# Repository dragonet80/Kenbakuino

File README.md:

# Kenbakuino
This is a fork from: https://github.com/funnypolynomial/Kenbakuino

This is in WIP state!

Arduino emulation of the KENBAK-1

This is an Arduino-based emulation of the 
[KENBAK-1](https://en.wikipedia.org/wiki/Kenbak-1 "Wikipedia"), considered by some to be the first "personal computer".  It was first advertised for sale in the September 1971 issue of Scientific American.

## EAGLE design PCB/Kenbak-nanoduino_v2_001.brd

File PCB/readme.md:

Fitxers per a la PCB en format Autodesk Eagle

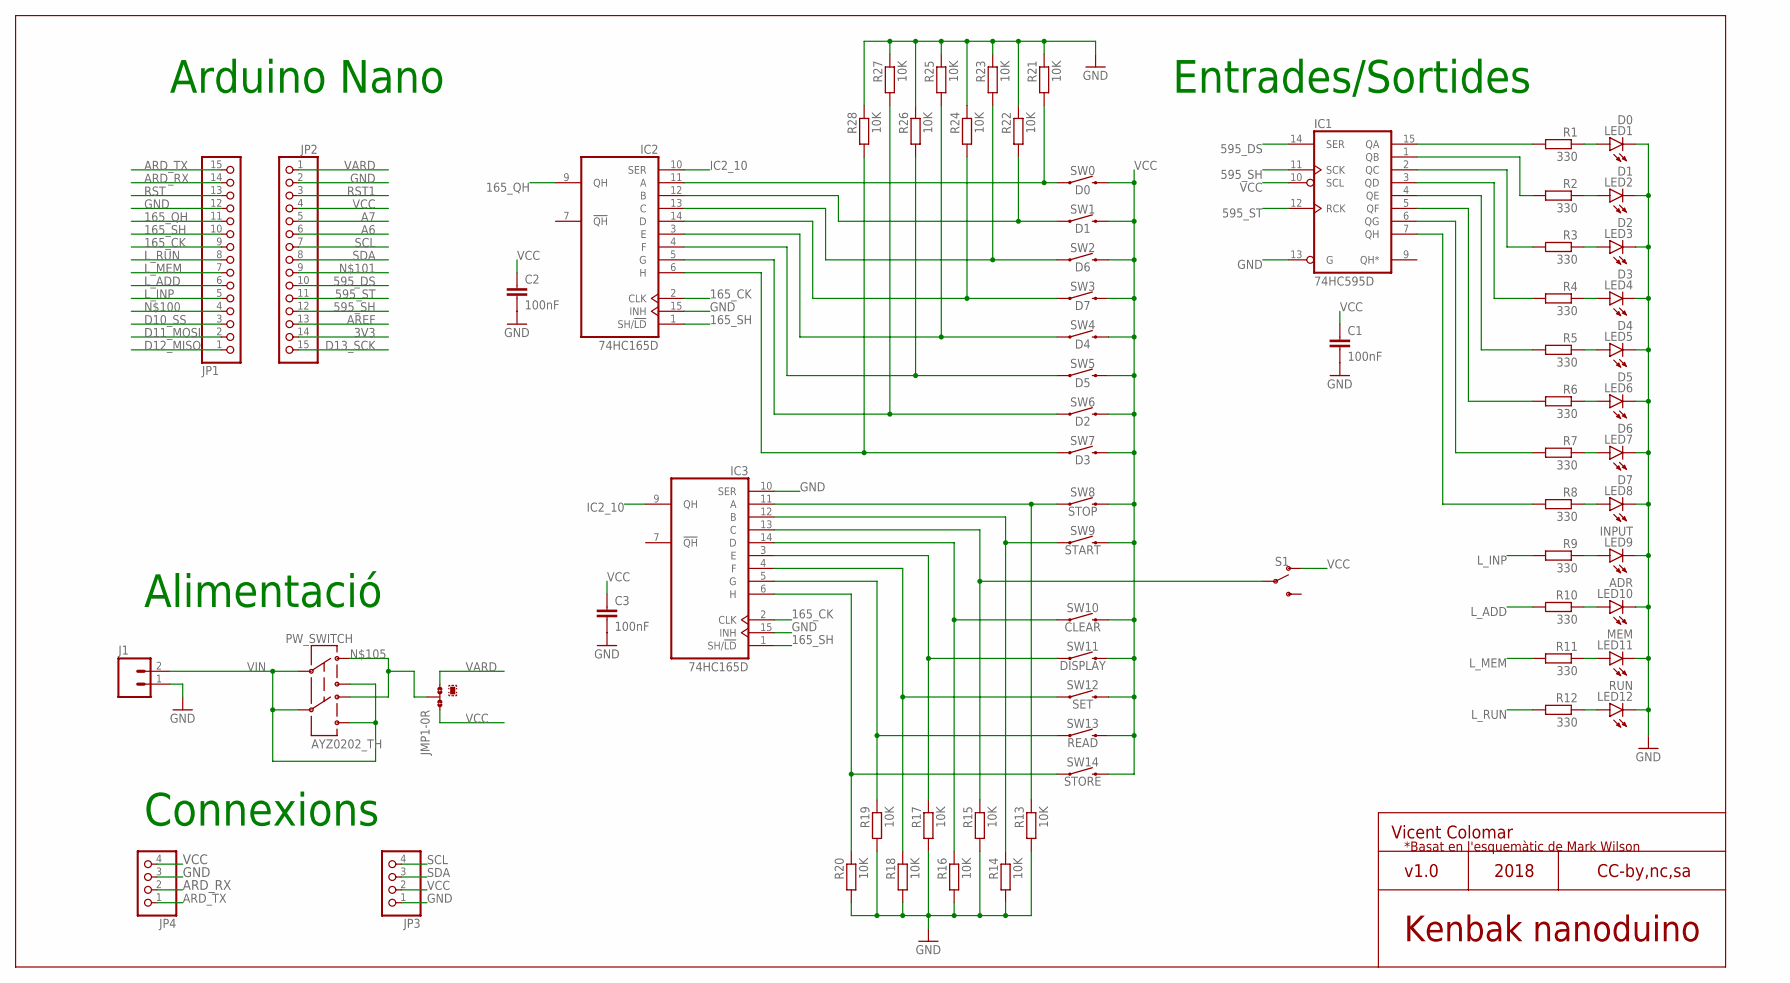
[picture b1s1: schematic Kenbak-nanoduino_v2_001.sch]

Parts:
C1, C2, C3: 100nF; C1206
IC1: 74HC595D; SO16
IC2, IC3: 74HC165D; SO16
J1: M02LOCK_LONGPADS; 1X02_LOCK_LONGPADS
JMP1: 0R-JUMPA; A0R-JMP
JP1, JP2: PINHD-1X15_2.54-SMD; 1X15SMD
JP3, JP4: PINHD-1X04_2.54-SMD; 1X04SMD
LED1: D0; LED3MM
LED2: D1; LED3MM
LED3: D2; LED3MM
LED4: D3; LED3MM
LED5: D4; LED3MM
LED6: D5; LED3MM
LED7: D6; LED3MM
LED8: D7; LED3MM
LED9: INPUT; LED3MM
LED10: ADR; LED3MM
LED11: MEM; LED3MM
LED12: RUN; LED3MM
PW_SWITCH: AYZ0202_TH
R1, R2, R3, R4, R5, R6, R7, R8, R9, R10, R11, R12: 330; R1206
R13, R14, R15, R16, R17, R18, R19, R20, R21, R22, R23, R24, R25, R26, R27, R28: 10K; R1206
S1: SWITCH-SPDT-PTH-11.6X4.0MM; SWITCH_SPDT_PTH_11.6X4.0MM
SW0: D0; TACTILE_SWITCH_SMD_6.0X3.5MM
SW1: D1; TACTILE_SWITCH_SMD_6.0X3.5MM
SW2: D6; TACTILE_SWITCH_SMD_6.0X3.5MM
SW3: D7; TACTILE_SWITCH_SMD_6.0X3.5MM
SW4: D4; TACTILE_SWITCH_SMD_6.0X3.5MM
SW5: D5; TACTILE_SWITCH_SMD_6.0X3.5MM
SW6: D2; TACTILE_SWITCH_SMD_6.0X3.5MM
SW7: D3; TACTILE_SWITCH_SMD_6.0X3.5MM
SW8: STOP; TACTILE_SWITCH_SMD_6.0X3.5MM
SW9: START; TACTILE_SWITCH_SMD_6.0X3.5MM
SW10: CLEAR; TACTILE_SWITCH_SMD_6.0X3.5MM
SW11: DISPLAY; TACTILE_SWITCH_SMD_6.0X3.5MM
SW12: SET; TACTILE_SWITCH_SMD_6.0X3.5MM
SW13: READ; TACTILE_SWITCH_SMD_6.0X3.5MM
SW14: STORE; TACTILE_SWITCH_SMD_6.0X3.5MM

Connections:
3V3: JP2.14
165_CK: IC2.2 (CLK), IC3.2 (CLK), JP1.9
165_QH: IC2.9 (QH), JP1.11
165_SH: IC2.1 (SH/!LD), IC3.1 (SH/!LD), JP1.10
595_DS: IC1.14 (SER), JP2.10
595_SH: IC1.11 (SCK), JP2.12
595_ST: IC1.12 (RCK), JP2.11
A6: JP2.6
A7: JP2.5
ARD_RX: JP1.14, JP4.2
ARD_TX: JP1.15, JP4.1
AREF: JP2.13
D10_SS: JP1.3
D11_MOSI: JP1.2
D12_MISO: JP1.1
D13_SCK: JP2.15
GND: C1.2, C2.2, C3.2, IC1.8 (GND), IC1.13 (G), IC2.8 (GND), IC2.15 (INH), IC3.8 (GND), IC3.10 (SER), IC3.15 (INH), J1.1, JP1.12, JP2.2, JP3.1, JP4.3, LED1.K (C), LED2.K (C), LED3.K (C), LED4.K (C), LED5.K (C), LED6.K (C), LED7.K (C), LED8.K (C), LED9.K (C), LED10.K (C), LED11.K (C), LED12.K (C), R13.2, R14.2, R15.2, R16.2, R17.2, R18.2, R19.2, R20.2, R21.1, R22.1, R23.1, R24.1, R25.1, R26.1, R27.1, R28.1
IC2_10: IC2.10 (SER), IC3.9 (QH)
L_ADD: JP1.6, R10.2
L_INP: JP1.5, R9.2
L_MEM: JP1.7, R11.2
L_RUN: JP1.8, R12.2
unnamed: LED1.A, R1.1
unnamed: LED2.A, R2.1
unnamed: LED3.A, R3.1
unnamed: LED4.A, R4.1
unnamed: LED5.A, R5.1
unnamed: LED6.A, R6.1
unnamed: LED7.A, R7.1
unnamed: LED8.A, R8.1
unnamed: LED9.A, R9.1
unnamed: LED10.A, R10.1
unnamed: LED11.A, R11.1
unnamed: LED12.A, R12.1
unnamed: IC1.15 (QA), R1.2
unnamed: IC1.1 (QB), R2.2
unnamed: IC1.2 (QC), R3.2
unnamed: IC1.3 (QD), R4.2
unnamed: IC1.4 (QE), R5.2
unnamed: IC1.5 (QF), R6.2
unnamed: IC1.6 (QG), R7.2
unnamed: IC1.7 (QH), R8.2
unnamed: IC2.11 (A), R21.2, SW0.1
unnamed: IC2.12 (B), R22.2, SW1.1
unnamed: IC2.13 (C), R23.2, SW2.1
unnamed: IC2.14 (D), R24.2, SW3.1
unnamed: IC3.13 (C), R15.1, S1.2
unnamed: IC2.3 (E), R25.2, SW4.1
unnamed: IC2.4 (F), R26.2, SW5.1
unnamed: IC2.5 (G), R27.2, SW6.1
unnamed: IC2.6 (H), R28.2, SW7.1
unnamed: IC3.11 (A), R13.1, SW8.1
unnamed: IC3.12 (B), R14.1, SW9.1
unnamed: IC3.14 (D), R16.1, SW10.1
unnamed: IC3.3 (E), R17.1, SW11.1
unnamed: IC3.4 (F), R18.1, SW12.1
unnamed: IC3.5 (G), R19.1, SW13.1
unnamed: IC3.6 (H), R20.1, SW14.1
unnamed: JMP1.2, PW_SWITCH.D1, PW_SWITCH.D2
RST: JP1.13
RST1: JP2.3
SCL: JP2.7, JP3.4
SDA: JP2.8, JP3.3
VARD: JMP1.3, JP2.1
VCC: C1.1, C2.1, C3.1, IC1.10 (SCL), IC1.16 (VCC), IC2.16 (VCC), IC3.16 (VCC), JMP1.1, JP2.4, JP3.2, JP4.4, S1.1 (O), SW0.2, SW1.2, SW2.2, SW3.2, SW4.2, SW5.2, SW6.2, SW7.2, SW8.2, SW9.2, SW10.2, SW11.2, SW12.2, SW13.2, SW14.2
VIN: J1.2, PW_SWITCH.B1, PW_SWITCH.B2, PW_SWITCH.C1, PW_SWITCH.C2

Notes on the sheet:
Alimentació
Arduino Nano
Kenbak nanoduino
v1.0
2018
CC-by,nc,sa
Vicent Colomar
Connexions
Entrades/Sortides
*Basat en l'esquemàtic de Mark Wilson

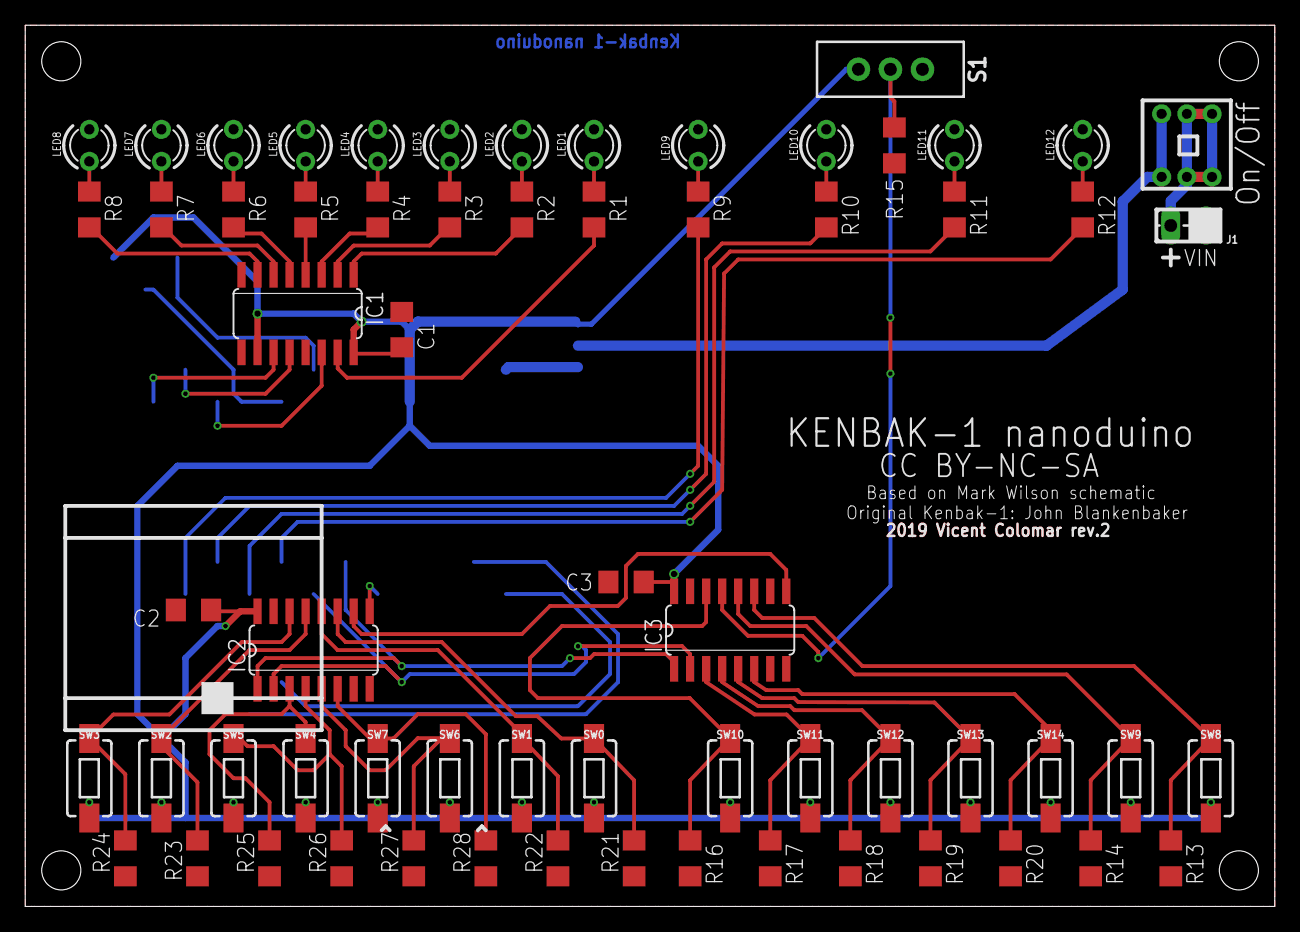
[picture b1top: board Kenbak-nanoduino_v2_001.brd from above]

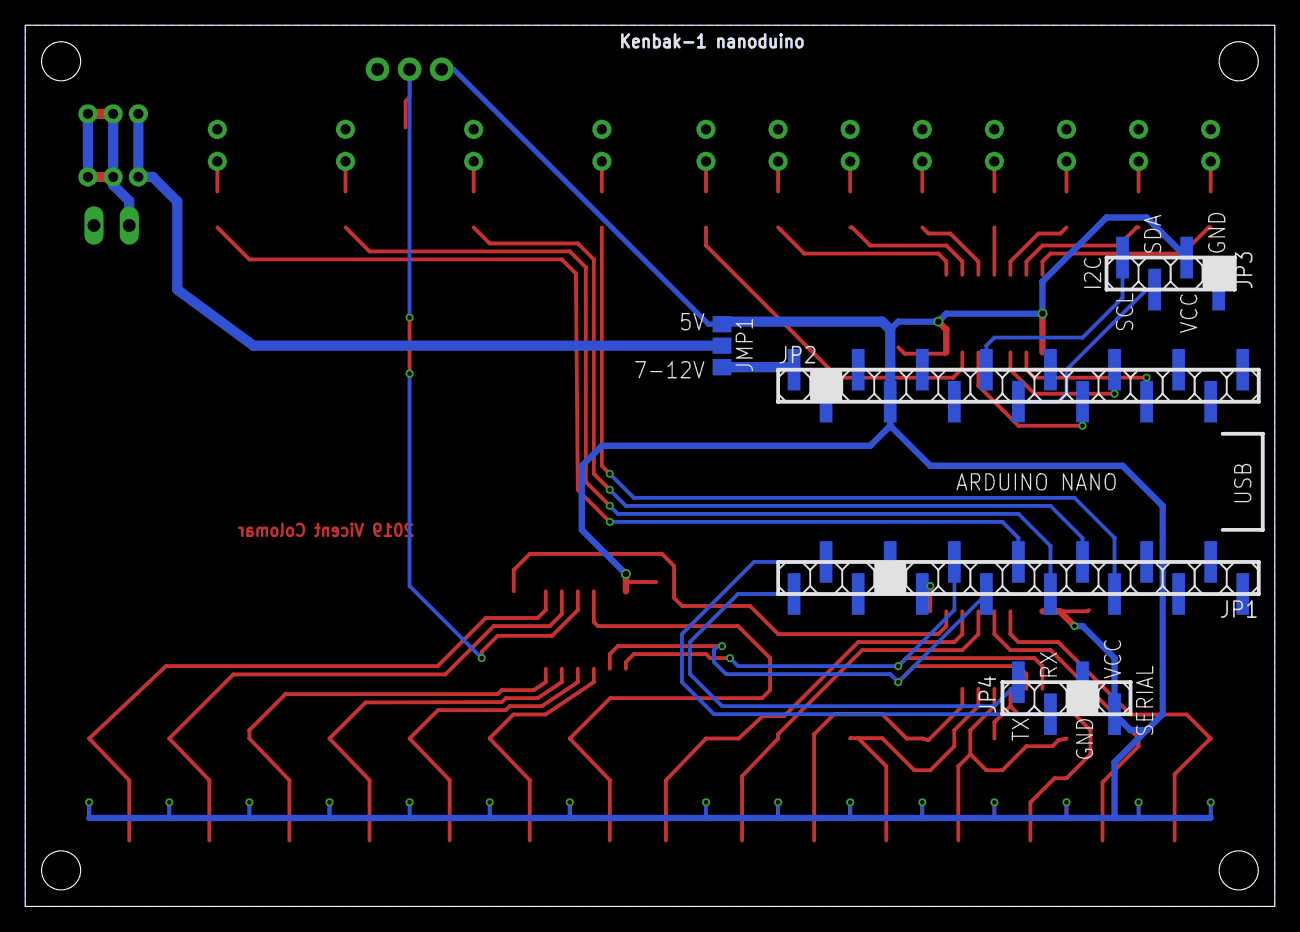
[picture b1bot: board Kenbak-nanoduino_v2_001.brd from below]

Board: 2 copper layers, 99.0 x 69.8 mm, 69 parts (5 on the bottom side), 56 nets.

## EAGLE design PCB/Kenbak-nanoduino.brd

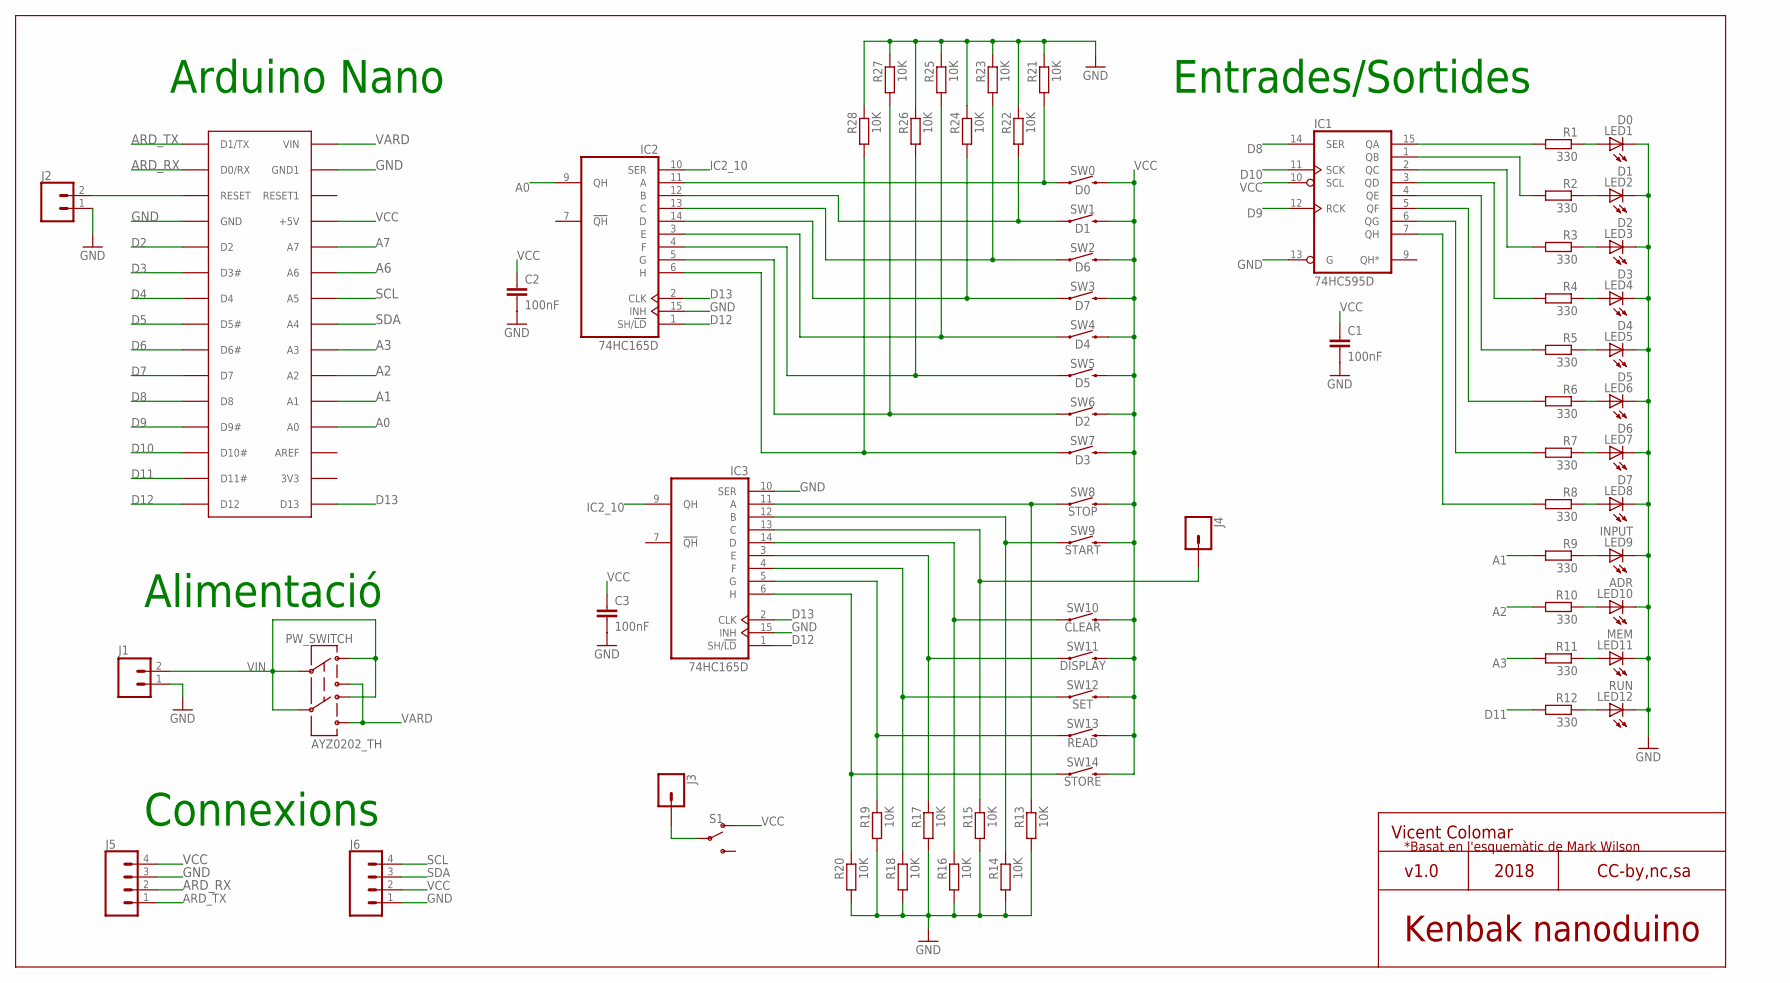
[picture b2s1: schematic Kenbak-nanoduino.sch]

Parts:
ARDUINO: NANO; PDIP-32NOHOLES
C1, C2, C3: 100nF; C1206
IC1: 74HC595D; SO16
IC2, IC3: 74HC165D; SO16
J1: M02LOCK_LONGPADS; 1X02_LOCK_LONGPADS
J2: CONN_02; 1X02
J3, J4: CONN_01; 1X01
J5, J6: CONN_04; 1X04
LED1: D0; LED3MM
LED2: D1; LED3MM
LED3: D2; LED3MM
LED4: D3; LED3MM
LED5: D4; LED3MM
LED6: D5; LED3MM
LED7: D6; LED3MM
LED8: D7; LED3MM
LED9: INPUT; LED3MM
LED10: ADR; LED3MM
LED11: MEM; LED3MM
LED12: RUN; LED3MM
PW_SWITCH: AYZ0202_TH
R1, R2, R3, R4, R5, R6, R7, R8, R9, R10, R11, R12: 330; R1206
R13, R14, R15, R16, R17, R18, R19, R20, R21, R22, R23, R24, R25, R26, R27, R28: 10K; R1206
S1: SWITCH-SPDT-PTH-11.6X4.0MM; SWITCH_SPDT_PTH_11.6X4.0MM
SW0: D0; TACTILE_SWITCH_PTH_6.0X3.5MM
SW1: D1; TACTILE_SWITCH_PTH_6.0X3.5MM
SW2: D6; TACTILE_SWITCH_PTH_6.0X3.5MM
SW3: D7; TACTILE_SWITCH_PTH_6.0X3.5MM
SW4: D4; TACTILE_SWITCH_PTH_6.0X3.5MM
SW5: D5; TACTILE_SWITCH_PTH_6.0X3.5MM
SW6: D2; TACTILE_SWITCH_PTH_6.0X3.5MM
SW7: D3; TACTILE_SWITCH_PTH_6.0X3.5MM
SW8: STOP; TACTILE_SWITCH_PTH_6.0X3.5MM
SW9: START; TACTILE_SWITCH_PTH_6.0X3.5MM
SW10: CLEAR; TACTILE_SWITCH_PTH_6.0X3.5MM
SW11: DISPLAY; TACTILE_SWITCH_PTH_6.0X3.5MM
SW12: SET; TACTILE_SWITCH_PTH_6.0X3.5MM
SW13: READ; TACTILE_SWITCH_PTH_6.0X3.5MM
SW14: STORE; TACTILE_SWITCH_PTH_6.0X3.5MM

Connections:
A0: ARDUINO.A0, IC2.9 (QH)
A1: ARDUINO.A1, R9.2
A2: ARDUINO.A2, R10.2
A3: ARDUINO.A3, R11.2
A6: ARDUINO.A6
A7: ARDUINO.A7
ARD_RX: ARDUINO.D0/RX, J5.2
ARD_TX: ARDUINO.D1/TX, J5.1
D2: ARDUINO.D2
D3: ARDUINO.D3 (D3#)
D4: ARDUINO.D4
D5: ARDUINO.D5 (D5#)
D6: ARDUINO.D6 (D6#)
D7: ARDUINO.D7
D8: ARDUINO.D8, IC1.14 (SER)
D9: ARDUINO.D9 (D9#), IC1.12 (RCK)
D10: ARDUINO.D10 (D10#), IC1.11 (SCK)
D11: ARDUINO.D11 (D11#), R12.2
D12: ARDUINO.D12, IC2.1 (SH/!LD), IC3.1 (SH/!LD)
D13: ARDUINO.D13, IC2.2 (CLK), IC3.2 (CLK)
GND: ARDUINO.GND, ARDUINO.GND1, C1.2, C2.2, C3.2, IC1.8 (GND), IC1.13 (G), IC2.8 (GND), IC2.15 (INH), IC3.8 (GND), IC3.10 (SER), IC3.15 (INH), J1.1, J2.1, J5.3, J6.1, LED1.K (C), LED2.K (C), LED3.K (C), LED4.K (C), LED5.K (C), LED6.K (C), LED7.K (C), LED8.K (C), LED9.K (C), LED10.K (C), LED11.K (C), LED12.K (C), R13.2, R14.2, R15.2, R16.2, R17.2, R18.2, R19.2, R20.2, R21.1, R22.1, R23.1, R24.1, R25.1, R26.1, R27.1, R28.1
IC2_10: IC2.10 (SER), IC3.9 (QH)
unnamed: LED1.A, R1.1
unnamed: LED2.A, R2.1
unnamed: LED3.A, R3.1
unnamed: LED4.A, R4.1
unnamed: LED5.A, R5.1
unnamed: LED6.A, R6.1
unnamed: LED7.A, R7.1
unnamed: LED8.A, R8.1
unnamed: LED9.A, R9.1
unnamed: LED10.A, R10.1
unnamed: LED11.A, R11.1
unnamed: LED12.A, R12.1
unnamed: IC1.15 (QA), R1.2
unnamed: IC1.1 (QB), R2.2
unnamed: IC1.2 (QC), R3.2
unnamed: IC1.3 (QD), R4.2
unnamed: IC1.4 (QE), R5.2
unnamed: IC1.5 (QF), R6.2
unnamed: IC1.6 (QG), R7.2
unnamed: IC1.7 (QH), R8.2
unnamed: IC2.11 (A), R21.2, SW0.P$1 (1)
unnamed: IC2.12 (B), R22.2, SW1.P$1 (1)
unnamed: IC2.13 (C), R23.2, SW2.P$1 (1)
unnamed: IC2.14 (D), R24.2, SW3.P$1 (1)
unnamed: J3.1, S1.2
unnamed: IC2.3 (E), R25.2, SW4.P$1 (1)
unnamed: IC2.4 (F), R26.2, SW5.P$1 (1)
unnamed: IC2.5 (G), R27.2, SW6.P$1 (1)
unnamed: IC2.6 (H), R28.2, SW7.P$1 (1)
unnamed: IC3.11 (A), R13.1, SW8.P$1 (1)
unnamed: IC3.12 (B), R14.1, SW9.P$1 (1)
unnamed: IC3.13 (C), J4.1, R15.1
unnamed: IC3.14 (D), R16.1, SW10.P$1 (1)
unnamed: IC3.3 (E), R17.1, SW11.P$1 (1)
unnamed: IC3.4 (F), R18.1, SW12.P$1 (1)
unnamed: IC3.5 (G), R19.1, SW13.P$1 (1)
unnamed: IC3.6 (H), R20.1, SW14.P$1 (1)
unnamed: ARDUINO.RESET, J2.2
SCL: ARDUINO.A5, J6.4
SDA: ARDUINO.A4, J6.3
VARD: ARDUINO.VIN, PW_SWITCH.B1, PW_SWITCH.B2
VCC: ARDUINO.+5V, C1.1, C2.1, C3.1, IC1.10 (SCL), IC1.16 (VCC), IC2.16 (VCC), IC3.16 (VCC), J5.4, J6.2, S1.1 (O), SW0.P$2 (2), SW1.P$2 (2), SW2.P$2 (2), SW3.P$2 (2), SW4.P$2 (2), SW5.P$2 (2), SW6.P$2 (2), SW7.P$2 (2), SW8.P$2 (2), SW9.P$2 (2), SW10.P$2 (2), SW11.P$2 (2), SW12.P$2 (2), SW13.P$2 (2), SW14.P$2 (2)
VIN: J1.2, PW_SWITCH.C1, PW_SWITCH.C2, PW_SWITCH.D1, PW_SWITCH.D2

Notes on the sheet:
Alimentació
Arduino Nano
Kenbak nanoduino
v1.0
2018
CC-by,nc,sa
Vicent Colomar
Connexions
Entrades/Sortides
*Basat en l'esquemàtic de Mark Wilson

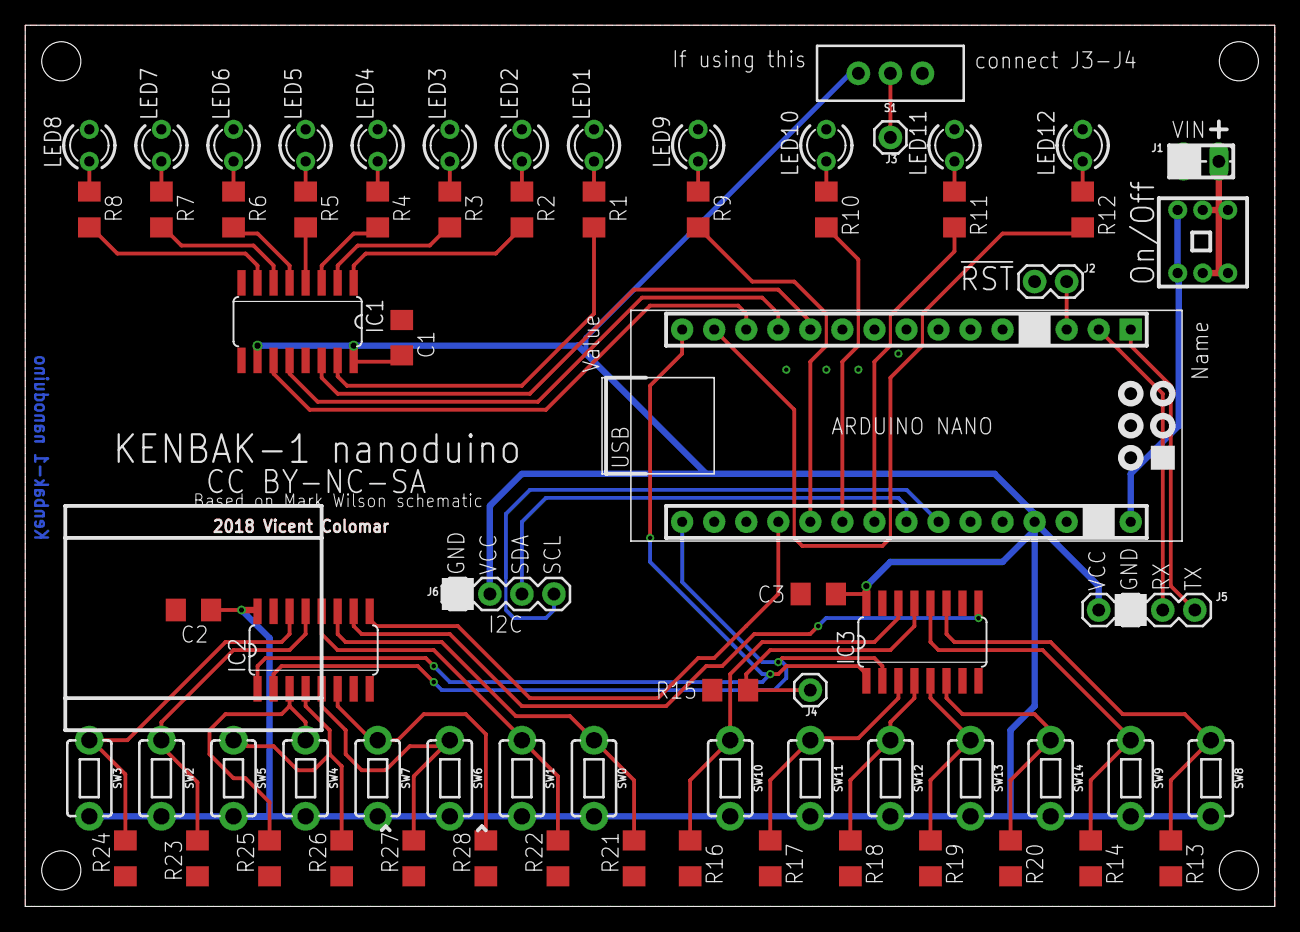
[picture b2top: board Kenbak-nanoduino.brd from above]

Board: 2 copper layers, 99.0 x 69.8 mm, 70 parts (0 on the bottom side), 57 nets.

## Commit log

2019-01-10 Update LEDS.cpp
    The shiftOut(PIN_LEDS_DS, PIN_LEDS_SH, LSBFIRST, LEDs) function results in inverted data led positions.
2024-10-27 Update README.md
    Actualitzades fotos reals

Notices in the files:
parts and their libraries:
SparkFun: Licensing: CC v3.0 Share-Alike You are welcome to use this library for commercial purposes.
dragonet80: Licensing: Creative Commons ShareAlike 4.0 International - https://creativecommons.org/licenses/by-sa/4.0
